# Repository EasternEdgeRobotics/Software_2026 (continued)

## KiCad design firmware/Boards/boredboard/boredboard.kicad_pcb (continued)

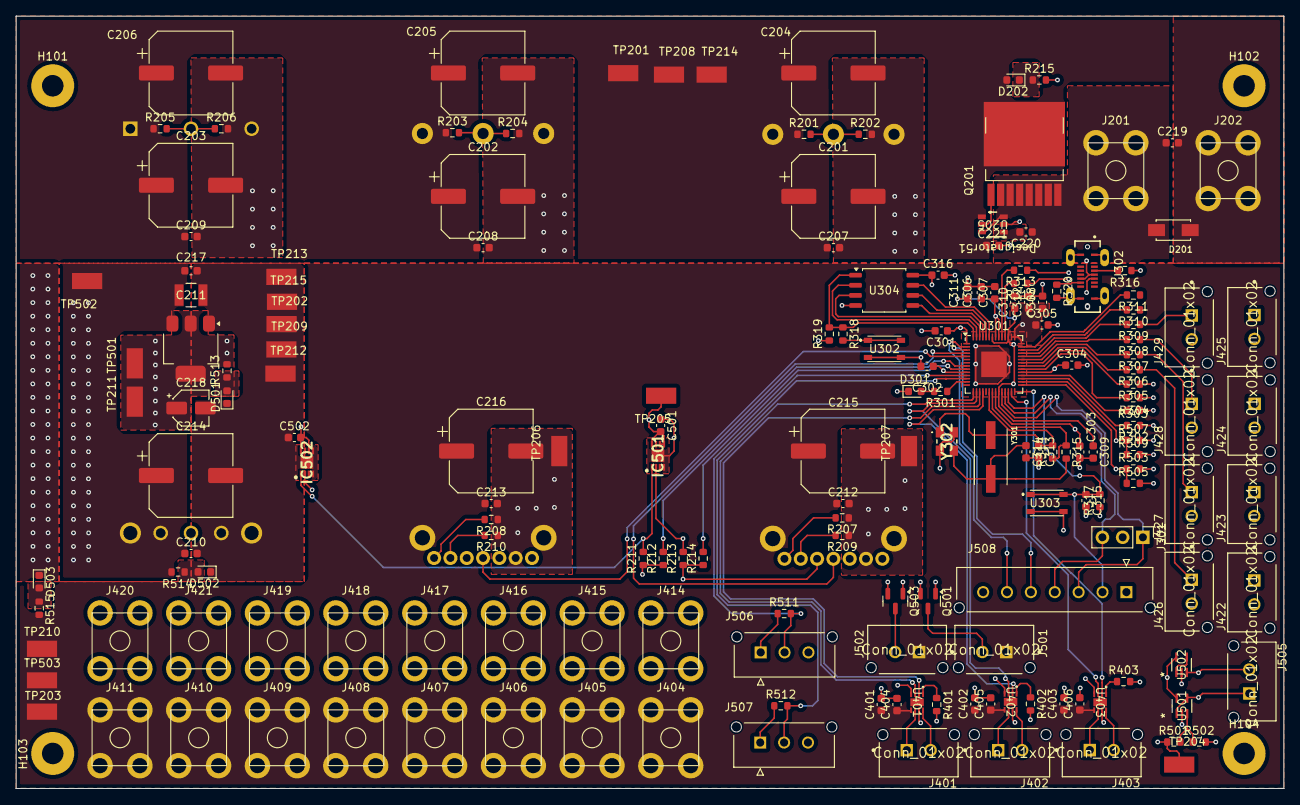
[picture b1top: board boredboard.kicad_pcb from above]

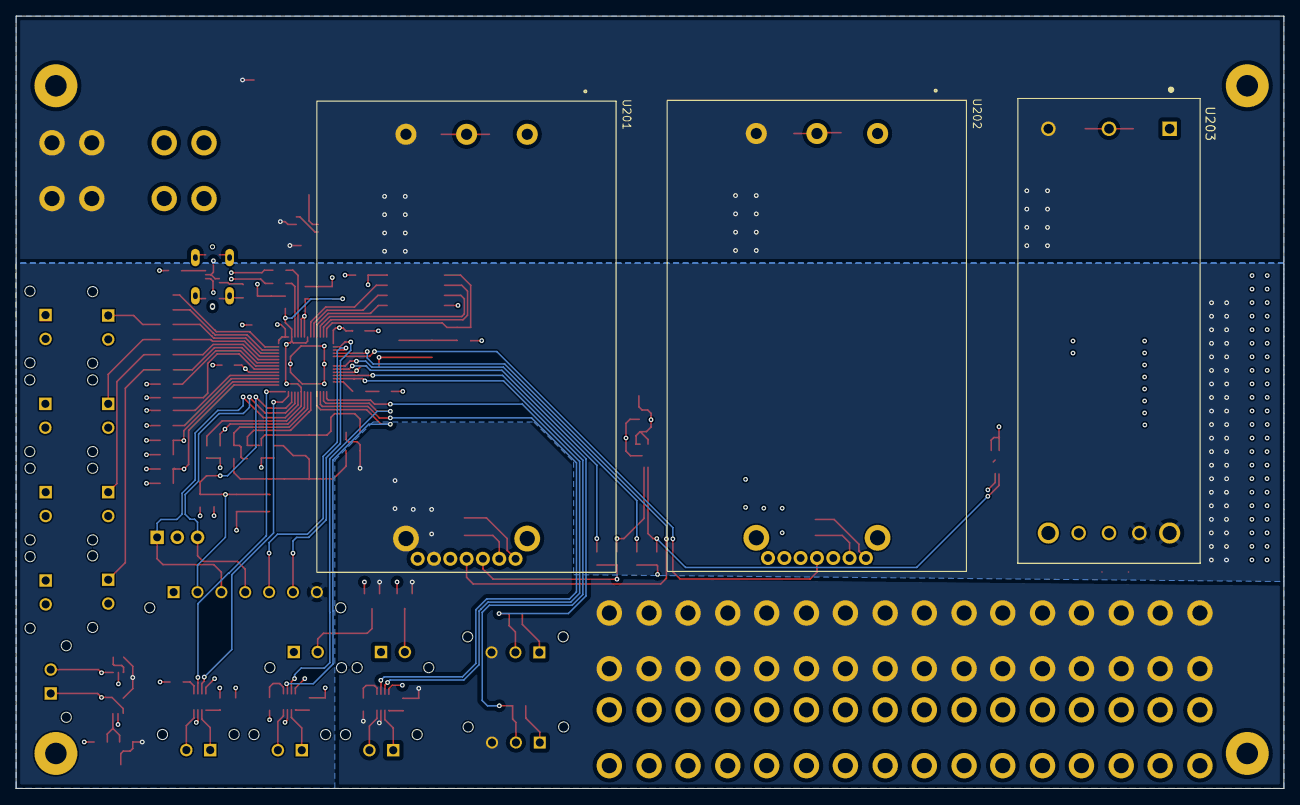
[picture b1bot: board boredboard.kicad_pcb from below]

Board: 4 copper layers, 159.3 x 97.0 mm, 180 parts (3 on the bottom side), 94 nets.

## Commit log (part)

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2025-11-18 Brought over 2025 software/firmware & converted i2c to uart
2025-11-22 2025 repo with i2c replaced with uart
2025-12-19 feat: moving 2026 firmware to use hdlc + message framing
2025-12-19 fix: remove git submoudle
2025-12-20 feat: pico code updated for LapisLazuli (not including motor control loop)
2025-12-20 fix: comment
2025-12-20 fix: compile errors and warnings
2025-12-23 feat: modified bluestar backend code to work with new firmware
2025-12-23 feat: updated frontend for bluestar
2025-12-23 fix: miswritten config
2025-12-23 fix: ROS.hpp
2025-12-23 fix: more ImGui slider issues and not breaking out arrays
2025-12-23 fix: update launch files
2025-12-23 fix: rename common_backend to config_manager
2025-12-23 fix: keyboard bindings remapped to avoid conflicts with power presets
2025-12-23 fix: do not latch dc motor direction input
2025-12-23 temp: adding logging for servo and pcdcm rotate commands
2025-12-23 feat: add a byte wrapper for logging
2025-12-24 fix: the logging wrapper for transmitted bytes was a bad idea
2025-12-26 feat: updated repository documentation + experimenting with AI agents w/ Github Copilot agents
2025-12-28 fix: framing offset bit and thruster value publishing bugs
2025-12-29 feat: added docker compose quickstart and refactored frontend
2026-04-22 Uploading because Keagan's laptop can't handle git, somehow.
2026-04-23 Setup folders and add camera configs
2026-04-25 Added files for crab detection
    Before running create a conda environment
    - conda create --name yolo-env1 python=3.12 -y
    - conda activate yolo-env1
    Then install the following dependencies
    - pip install ultralytics
    - pip install --upgrade torch torchvision torchaudio --index-url https://download.pytorch.org/whl/cu124
2026-04-30 Add Cloudinit files for cameras
2026-04-30 Revert Repo to WW code
2026-04-30 Fix: Set default config menu size
2026-04-30 Remove refrences to bilge pump
2026-04-30 More beaumont cleanup
2026-04-30 Fix resizing config menu
2026-05-01 Add support for second LED channel and dimming LEDs
2026-05-01 Improve implemenation of LEDs, fix low side led bounds
2026-05-02 Update readmes and add back docker dev setup
2026-05-02 Remove refrences to SSH Servos
2026-05-02 Add servo support
2026-05-02 Fix macvlan ip overlapping with actual ip on BS
2026-05-02 Add BlueStar main pi and TestStar configs
2026-05-02 Fix servo behavior
2026-05-02 Fix servo behavior pt 2
2026-05-03 Fix servo behavior pt 3
2026-05-03 Fix server behavior pt 4
2026-05-03 Fix servo behavior pt 5
2026-05-03 FIx servo behevior pt 6
2026-05-03 Fix servo behavior pt 8
2026-05-03 Fix servo behavior pt 9
2026-05-03 Fix servo behavior pt 10
2026-05-03 Fix servo behavior pt 11
2026-05-03 Fix servo behavior pt 12
2026-05-03 Cleaning up 9 trillion if statements
2026-05-03 un-breaking the thing i broke while cleaning up
2026-05-03 ok how did i miss ANOTHER [i]
2026-05-03 ok fine i give up
2026-05-03 Move LED brightness adj to topside
2026-05-03 Fixed missing semicolon
2026-05-03 Fix out of range for loop
2026-05-03 Remove LED debug display
2026-05-03 Fix servo behavior pt 14
2026-05-03 Minor bug fixes
2026-05-03 Add comments to prevent future minecraft lets play series commits
2026-05-05 Switch from glew to glad
2026-05-05 Add semi-functional webrtc support
2026-05-05 Fix simultanous webrtc streams
2026-05-05 Add rswebrtc build script
2026-05-05 Minor install script fixes, add missing deps to dockerfile and update docs
2026-05-05 WebRTC: Add auto-recovery
2026-05-05 Switch camera config to table
2026-05-06 Add catch for invalid points w/ 4 points
2026-05-07 Switch to dif cam
2026-05-07 Add "About GUI" menu (relavant for future changes)
2026-05-11 Prepare for webrtcbin backend
2026-05-11 Add camera caps to UI and config
2026-05-11 Improve camera logging (Add unique labels for each camera
2026-05-11 Minor changes - Fix camera 4 vertical flip button in GUI - Allow for setting buffers easier in both webrtcbin and whepclientsrc backends - Change default backend to webrtcbin
2026-05-11 Remove drop from fakesink, set webrtcbin jitter buffer latency to 10ms
2026-05-11 Add documentation for building different camera backends
2026-05-13 Add window state to userconfig
2026-05-13 Add app id for better gnome compat
2026-05-13 Add screenshots from controller
2026-05-14 Add bluestar icon
2026-05-14 Add basic science officer GUI
2026-05-14 Screenshot system improvements: - Make screenshots async in both bluestar_frontend and bluestar_officer_frontend. - Fix screenshot buttons in bluestar_frontend if keyboard mode is off and no controll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
2026-05-14 Add extra info to screenshot file names in bluestar_frontend and bluestar_officer_frontend
2026-05-14 Add screenshot cropping
2026-05-14 Remove science officer GUI from dockerfile
2026-05-14 Science officer GUI visual improvements
2026-05-17 Add exif data modifer script
2026-05-17 Update backend docker compose to match current network setup
2026-05-17 fix backend docker compose
2026-05-17 Fix DC motors pt 2
2026-05-17 Flip DC motor registers to match BlueStar positions
2026-05-18 Add basic script to automate webodm uploads
2026-05-18 Fix EXIF extended metadata
2026-05-18 Switch folder structure for saving images in bluestar_officer_frontend
2026-05-18 Science Officer changes - Add folder structure for science officer related tools - Add webodm uploading to science officer GUI - Add photo counter to science officer GUI
2026-05-18 Adjust file structure
2026-05-18 Add readme to science officer folder
2026-05-18 Fix typo
2026-05-18 Add cli args
2026-05-18 Improve text clarity
2026-05-19 Add support for MPS on macOS to speed up inference and minor fixes
2026-05-19 Add CoreML support on macos and add CoreML version of model
2026-05-19 Add ffmpeg source backend
2026-05-19 Add ffmpeg backend to iceburg depth calculation
2026-05-19 remove .vscode
2026-05-22 Add webodm bruteforce script
2026-05-22 Science officer - Invasive crabs: Add keyboard control for threshold and display in GUI
2026-05-22 Science Officer - Coral Garden: Update settings in webodm_upload.py
2026-05-22 Minor Science officer changes: - Switch keys used in crab, iceberg and coral garden scripts to match eachother. - Add list of keys for each script to their respective readmes.
2026-05-22 Add 2nd val to coral garden pixel measurement
2026-05-23 Add magnifer to coral garden and iceberg measurement tools
2026-05-23 Add fisheye correction
2026-05-23 Science officer: move common functionaltiy to llibraries
2026-05-23 Add camera calibration script
2026-05-23 Calibration fixes
2026-05-23 Move zoom cursor drawing after the lines and increase size of cursor
2026-05-23 Move text readouts to top right corner and set point colour based off index
2026-05-23 Science Officer - Coral garden and Iceberg measurement: - Allow for unfreezing the stream - Allow for resetting the measured points
2026-05-23 Science Officer - Coral Garden: Update WebODM URL to match VMware Fusion NAT address
2026-05-23 Science Officer - Invasive Crabs: add new model and organize models
2026-05-24 Science Officer Coral + Iceberg fixes and improvements: - Add fisheye toggle using keyboard - Add pinhole correction support - Fix calibration script
2026-05-24 Science Officer Coral + Crab + Iceberg Improvements: - Move video source constructor into frame_capture.py - Fix fisheye correction on iceberg and coral - Add warning for invalid fisheye correction v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
2026-05-25 Sciene Officer - Iceberg Measurement Improvements: - Use 15cm pole on other side of unknown as reference - Add line guide for cursor - Fixed points not resetting if invalid
2026-05-25 Science Officer - Coral Garden Improvements: - Add improved measurement system that came to me in a dream
2026-05-25 Science Officer - Coral Garden Fixes: - Fixes that didnt come to me in a dream
2026-05-25 Science Officer: Fix typos
2026-05-30 Science Officer - Minor fixes and improvements: - Add fluf value to coral garden scaler - Fix missing arg in coral garden scaler readme - Add fluf value for iceberg measurement w/ vertical pole enabl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
2026-05-30 Add launch script for flume task science officer tasks
2026-05-30 Science Officer - Launch script: Fix cameras being set to wrong URLs
2026-05-30 Science officer - launch script fixes
2026-05-30 BlueStar Frontend Improvements: Update default crop values
2026-05-31 Science Officer Frontend: Add basic support for rosless setup
2026-05-31 Science Officer Frontend: Improve macOS support
2026-05-31 Science Officer Frontend and Launch script: WebODM Fixes
2026-06-02 Science Officer Coral Garden: Update WebODM settings
2026-06-02 Science Officer Coral Garden: Improve settings to reduce time and increase quality
2026-06-02 Science Officer Coral and Iceberg improvements: - Add updated sheet with macro to auto clear values (Thanks Ben!) - Adjust WebODM settings
2026-06-02 Science Officer launch script: Update sheet to use versin with macro
2026-06-02 BlueStar Science Officer GUI improvements: - Removing remaining ROS leftovers - Add build info
2026-06-03 Science Officer GUI - Update git submodules
2026-06-03 Science Officer GUI: Move out of ros_workspace
2026-06-04 Science Officer Task Fixes: - Update Spreadsheet. Thanks Ben! - Adjust coral garden fluf value - Fix launch script
2026-06-05 Science Officer: Launch Script Fixes: - Add sleeps to launch script to improve reliabiltiy
2026-06-12 Science Officer Coral Garden: Add realitykit based photogramatry engine
2026-06-12 Update gitignore to ignore swift build files
2026-06-12 Add realitykit batch tester
2026-06-12 Science Officer Coral Garden: Add compatability layer for existing infra in science officer GUI
2026-06-12 Science Officer GUI Improvements: - Switch to realitykit compatability script for photogramatry - Add VET to science officer GUI - Switch UI references to webodm to be generic.
2026-06-12 Science Officer RealityKit Coral Garden: Fix not returning status on exit
2026-06-12 Science Officer RKit Coral Garden: update readme with new os requirements
2026-06-12 Science Officer GUI: Add macOS dependancies
2026-06-12 Science Officer Frontend: Add photogrammetry script location to config
2026-06-12 Science Officer RKit Coral Garden: Add check for macOS
2026-06-13 Science Officer Rkit coral garden fixes: - Update cli help to reflect current naming and newer features
2026-06-14 Science Officer GUI: remove leftover files from old location
2026-06-14 BlueStar Frontend: Add basic reset ESC key support
2026-06-14 BlueStar Frontend Improvements: - Allow toggiling fast mode without keyboard mode - Switch copilot key detection to use glfw for consistency
2026-06-14 Science Officer Shared Improments: - Add auto reconnect to python scripts - Add no signal image while connection not available
2026-06-18 Science Officer Iceberg Measurement Improvements: - Add grid mode for measuring - Update launch script to enable grid mode by default - Fix TOP_PIPE_REF_CM not being used with vertical pipe mode disa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
2026-06-19 Science Officer Launch Script: Fix iceberg
2026-06-19 Science Officer Iceberg Improvements: - Debug mode w/ adj values for fluf and grid. - Switch grid to iceberg shaped grid - use copy of frame before grid or lines added to improve visabiltiy
2026-06-20 Science Officer Iceberg: Show lines in zoom cursor
2026-06-20 Science Officer Icerberg legth fix
2026-06-20 Science Officer Iceberg: Adjust top pipe ref
2026-06-22 Science Officer Iceberg: Make line outside draw mode translucent and stop drawing circles at points
2026-06-22 Science Officer Frontend: Remove camera rotation
2026-06-22 Science Officer Launch Script: Remove example PDF launch
2026-06-22 Science Officer Invasive Crabs: Move text for improved UX
2026-06-22 Science Officer Iceberg: car tricks!
2026-06-22 Science Officer Iceberg: expose adj outside debug mode
2026-06-22 Launch Script: Stop opening webodm webpage for coral garden
2026-06-22 BlueStar Frontend: adjust VET crop
2026-06-23 Science Officer Invasive Crabs: fix label for crab detection
2026-06-24 Launch Script: Add iceberg mapping to iceberg launch
2026-06-24 Science Officer Iceberg: Set lat and lon sec to 00 by default
2026-06-24 Science Officer Iceberg: Update README
